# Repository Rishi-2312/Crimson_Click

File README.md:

# Crimson_Click
The Crimson Click is a custom, high-performance 6-key macropad featuring an integrated rotary encoder. It is powered by the Seeed Studio XIAO RP2040, a compact and powerful microcontroller that provides fast response times. It consists of the Cherry MX switches and the EC11 encoder. Built on the RP2040 architecture, ensuring plenty of memory for complex macros, layers. The keys are protected by the DSA Keycaps. 

# Features
- Seeed Studio XIAO RP2040
- 6 keys
- 1x EC11 Rotary encoder
- Sandwich-style Case
- 4x M3 Bolts
# CAD MODEL:
Everything (the case and the plate) fits together using 4 M3 Bolts.
Crimson-click has 2 separate pieces which are connected by these bolts. The keys are covered by the DSA keycaps.

Made in Fusion 360.
# PCB
Here's my PCB. It was made in KiCad.

Schematic

PCB
# Firmware Overview
- The rotary encoder has functions of volume up and down; press to mute.
- The 6 keys have all different functions.
# BOM:
- 6x Cherry MX switches
- 6x DSA keycaps
- 4x M3 Bolts
- 1x XIAO RP2040
- 1X EC11 Rotary Encoder
- 1x Case
- 1x USB Type-C cable

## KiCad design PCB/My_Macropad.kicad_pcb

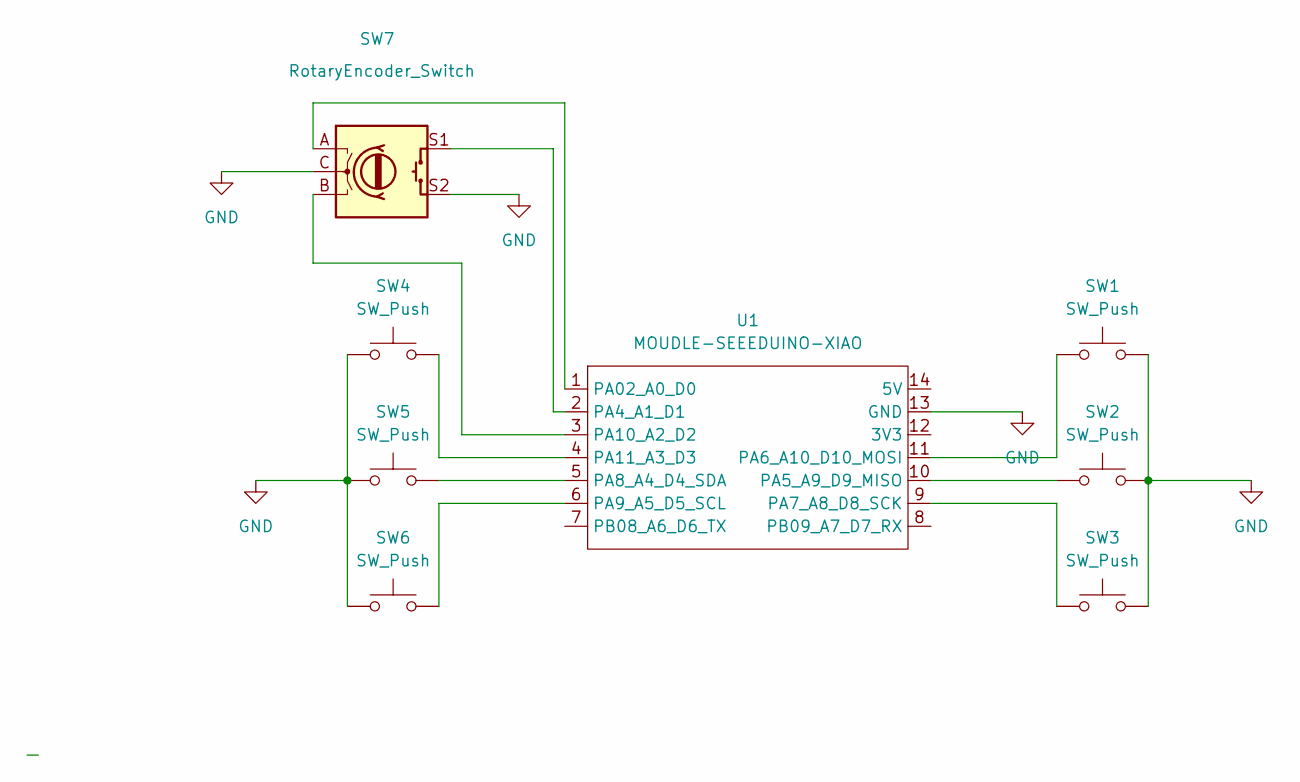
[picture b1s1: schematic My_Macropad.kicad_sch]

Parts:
SW1, SW2, SW3, SW4, SW5, SW6: SW_Push; SW_Cherry_MX_1.00u_PCB
SW7: RotaryEncoder_Switch; RotaryEncoder_Alps_EC11E-Switch_Vertical_H20mm
U1: MOUDLE-SEEEDUINO-XIAO; XIAO-Generic-Hybrid-14P-2.54-21X17.8MM

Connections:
GND: SW1.2, SW2.2, SW3.2, SW4.1, SW5.1, SW6.1, SW7.C, SW7.S2, U1.13 (GND)
unnamed: SW7.A, U1.1 (PA02_A0_D0)
unnamed: SW7.S1, U1.2 (PA4_A1_D1)
unnamed: SW2.1, U1.10 (PA5_A9_D9_MISO)
unnamed: SW1.1, U1.11 (PA6_A10_D10_MOSI)
unnamed: SW3.1, U1.9 (PA7_A8_D8_SCK)
unnamed: SW5.2, U1.5 (PA8_A4_D4_SDA)
unnamed: SW6.2, U1.6 (PA9_A5_D5_SCL)
unnamed: SW7.B, U1.3 (PA10_A2_D2)
unnamed: SW4.2, U1.4 (PA11_A3_D3)

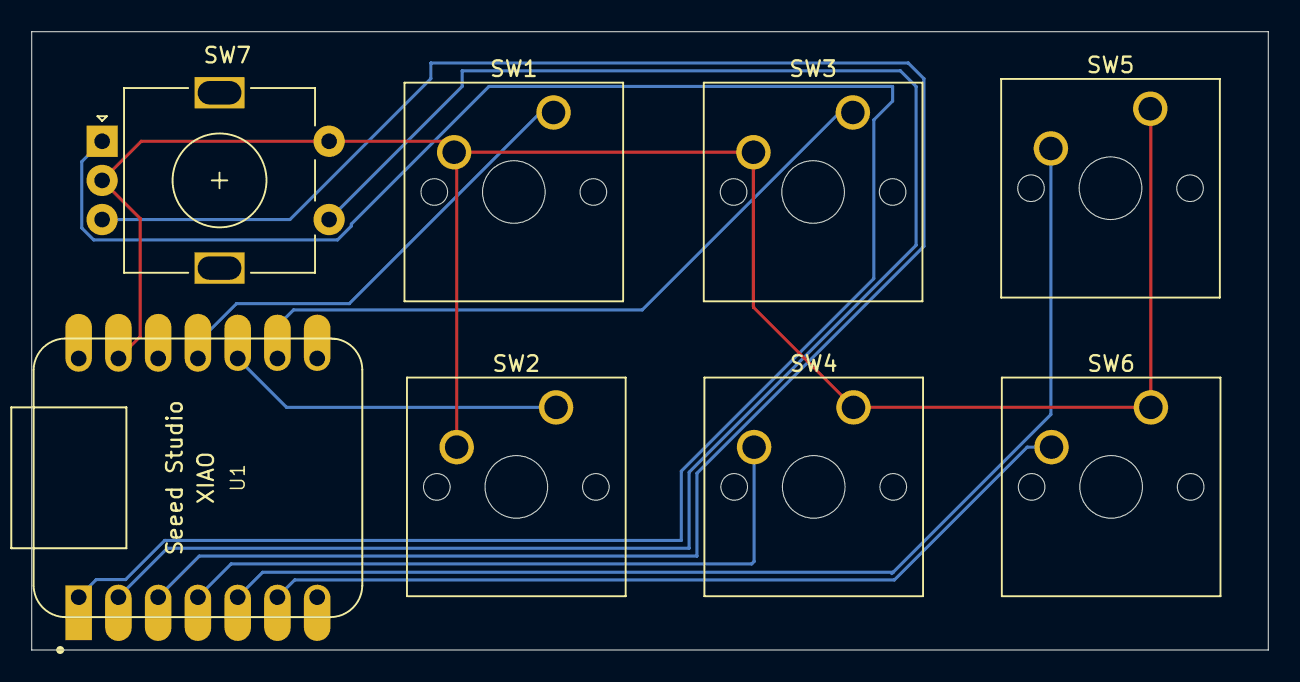
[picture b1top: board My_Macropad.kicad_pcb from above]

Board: 2 copper layers, 79.0 x 39.5 mm, 8 parts (0 on the bottom side), 10 nets.

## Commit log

2026-03-31 Create cad
2026-03-31 Create pcb
2026-03-31 Create Firmware
2026-03-31 Create production
2026-03-31 Create assets
